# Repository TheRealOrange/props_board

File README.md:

# props_board
ESP32 based control board for costumes and props featuring USB PD enabled charging

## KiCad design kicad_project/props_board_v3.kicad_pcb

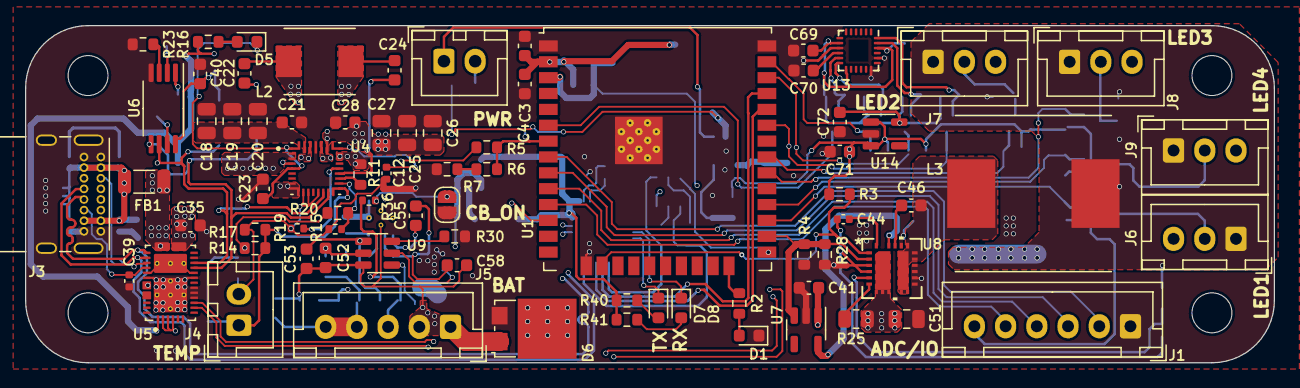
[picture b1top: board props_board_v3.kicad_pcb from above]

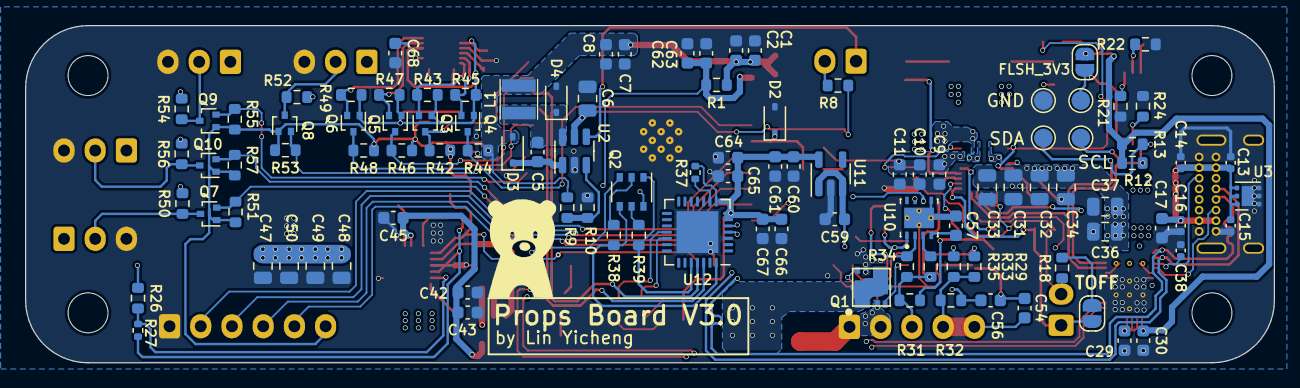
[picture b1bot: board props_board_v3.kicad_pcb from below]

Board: 4 copper layers, 100.0 x 27.0 mm, 187 parts (105 on the bottom side), 104 nets.

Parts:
C1, C2, C7, C8, C9, C10, C29, C30, C43, C61: 10u; C_0603_1608Metric
C3, C4, C5, C11, C21, C28, C35, C40, C41, C42, C46, C52, C53, C54, C55, C56, C58, C59, C60, C62, C63, C65, C67, C68, C69, C70, C71: 100n; C_0603_1608Metric
C6, C18, C19, C20, C25, C26, C27, C31, C32, C33, C34: 10u; C_0805_2012Metric
C12: 1000p; C_0402_1005Metric
C13, C14, C15, C16, C44: 10n; C_0402_1005Metric
C17, C23, C45, C64, C66: 4.7u; C_0603_1608Metric
C22, C24: 47n; C_0603_1608Metric
C36, C37, C47, C48, C49, C50, C51: 22u; C_0805_2012Metric
C38, C39: 330p; C_0402_1005Metric
C57: 330n; C_0603_1608Metric
C72: 1u; C_0603_1608Metric
D1, D5, D7, D8: LED; LED_0603_1608Metric
D2: MM3Z3V0ST1G; D_SOD-323
D3: 1N4148; D_SOD-323
D4: B5819WS; D_SOD-323
D6: SS10P4C; TO-277A
FB1: BLM31SN500SH1L; L_1206_3216Metric
H1, H2, H3, H4: MountingHole; MountingHole_3.2mm_M3_DIN965
J1: Conn_01x06; JST_XH_B6B-XH-A_1x06_P2.50mm_Vertical
J2: PWR; JST_XH_B2B-XH-A_1x02_P2.50mm_Vertical
J3: USB_C_Receptacle_USB2.0; USB_C_Receptacle_GCT_USB4085
J4: Conn_01x02; JST_XH_B2B-XH-A_1x02_P2.50mm_Vertical
J5: Conn_01x05; JST_XH_B5B-XH-A_1x05_P2.50mm_Vertical
J6: LED1; JST_XH_B3B-XH-A_1x03_P2.50mm_Vertical
J7: LED2; JST_XH_B3B-XH-A_1x03_P2.50mm_Vertical
J8: LED3; JST_XH_B3B-XH-A_1x03_P2.50mm_Vertical
J9: LED4; JST_XH_B3B-XH-A_1x03_P2.50mm_Vertical
JP1, JP2, JP3: Jumper_2_Open; SolderJumper-2_P1.3mm_Open_RoundedPad1.0x1.5mm
L1: 15u; TYA3012
L2: 1u; IND_ASPI-0530HI-1R0M-T2
L3: 3.3u; INDM1250X1250X600
NT1, NT2: NetTie_2; NetTie-2_SMD_Pad0.5mm
Q1: AON7804; DFN3X3
Q2: BC817DS; TSOP-6_1.65x3.05mm_P0.95mm
Q3, Q4, Q5, Q6, Q7, Q8, Q9, Q10: RE1C002UNTCL; SOT-416
R1, R3, R4, R5, R6, R7, R8, R10, R18, R21, R22, R23, R24, R28, R38, R39: 10k; R_0603_1608Metric
R2, R12, R13, R16, R30, R40, R41, R42, R43, R44, R45, R46, R47, R48, R49, R50, R51, R52, R53, R54, R55, R56, R57: 2k2; R_0603_1608Metric
R9, R17, R20, R26: 31.6k; R_0603_1608Metric
R11, R32, R35: 100; R_0603_1608Metric
R14: 5.23k; R_0603_1608Metric
R15, R36: 100k; R_0402_1005Metric
R19, R27: 6.04k; R_0402_1005Metric
R25: 200k; R_0805_2012Metric
R29, R31, R34: 270; R_0603_1608Metric
R33: 160; R_0603_1608Metric
R37: 1k; R_0402_1005Metric
TP1: FLSH_3V3; TestPoint_Pad_D1.5mm
TP2: SDA; TestPoint_Pad_D1.5mm
TP3: SCL; TestPoint_Pad_D1.5mm
TP4: GND; TestPoint_Pad_D1.5mm
U1: ESP32-WROOM-32U
U2: MCP16301; SOT-23-6
U3: TVS2200DRV; WSON-6-1EP_2x2mm_P0.65mm_EP1x1.6mm
U4: BQ25798RQMR; IC_BQ25798RQMR
U5: TPS25750DRJKR; IC_TPS25750DRJKR
U6: CAT24C256; TSSOP-8_4.4x3mm_P0.65mm
U7, U11: AP7375; SOT-23-5
U8: AOZ2261AQI-15; QFN4X4-22L_EP2_S_AOS
U9: S-8252; SOT-23-6
U10: BQ29209DRBR; SON65P300X300X100-9N
U12: CP2102N-Axx-xQFN28; QFN-28-1EP_5x5mm_P0.5mm_EP3.35x3.35mm
U13: ICM-20948; InvenSense_QFN-24_3x3mm_P0.4mm
U14: TLV74118; SOT-23-5

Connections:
/3V3: C1.1, C2.1, C3.1, C4.1, C7.1, C8.1, C71.1, D3.2 (A), J1.6, L1.2, Q7.1 (G), Q8.1 (G), Q9.1 (G), Q10.1 (G), R1.1, R3.1, R9.1, R42.1, R44.1, R46.1, R48.1, R51.1, R53.1, R55.1, R57.1, U1.2 (VDD), U14.1 (VIN), U14.3 (EN)
/3V3_EN: J2.1, U2.4 (EN)
/3V3_SW: C5.1, D4.1 (K), L1.1, U2.6 (SW)
/5V_PWR: C47.1, C48.1, C49.1, C50.1, J6.1, J7.1, J8.1, J9.1, L3.2, R26.1, R50.1, R52.1, R54.1, R56.1
/ADC1_CH4_GPIO: J1.2, U1.8 (IO32)
/ADC1_CH5_GPIO: J1.3, U1.9 (IO33)
/ADC2_CH8_GPIO: J1.4, U1.10 (IO25)
/ADC2_CH9_GPIO: J1.5, U1.11 (IO26)
/BAT_MON: C9.1, C10.1, C11.1, C54.1, J5.4, J5.5, R5.1, R11.2, R29.2, R32.1, R33.2, U4.22 (BAT), U4.23 (BAT__1)
/CB_EN: JP1.2 (B), R36.2, U1.12 (IO27), U10.6 (~CB_EN)
/EN: C62.1, C63.1, Q2.6 (C1), R1.2, U1.3 (EN)
/EN_5V: R4.1, R28.1, U1.26 (IO4), U7.3 (EN), U8.2 (EN)
/ESP_RXD: U1.34 (RXD0/IO3), U12.26 (TXD)
/ESP_SCL: Q5.3 (D), R46.2, U1.36 (IO22), U5.9 (I2CS_SCL)
/ESP_SDA: Q6.3 (D), R48.2, U1.33 (IO21), U5.8 (I2CS_SDA)
/ESP_TXD: U1.35 (TXD0/IO1), U12.25 (RXD)
/FSYNC: Q4.3 (D), R44.2, U1.6 (IO34)
/IND_LED: R2.1, U1.24 (IO2)
/INT: Q3.3 (D), R42.2, U1.37 (IO23)
/IO0: Q2.3 (C2), U1.25 (IO0)
/LED1: Q7.2 (S), R51.2, U1.27 (IO16)
/LED2: Q8.2 (S), R53.2, U1.31 (IO19)
/LED3: Q9.2 (S), R55.2, U1.30 (IO18)
/LED4: Q10.2 (S), R57.2, U1.28 (IO17)
/PGOOD_5V: R3.2, U1.16 (IO13), U8.1 (PGOOD)
/VBAT_SENSE: D2.1 (K), R5.2, R6.1, U1.7 (IO35)
/battery_charging/CC1: C38.1, J3.A5 (CC1), U5.28 (CC1)
/battery_charging/CC2: C39.1, J3.B5 (CC2), U5.29 (CC2)
/battery_charging/C_USB_N: J3.A7 (D-), J3.B7 (D-), U5.27 (GPIO5(USB_N)), U12.5 (D-)
/battery_charging/C_USB_P: J3.A6 (D+), J3.B6 (D+), U5.26 (GPIO4(USB_P)), U12.4 (D+)
/battery_charging/FLASH_3V3: C40.1, JP3.1 (A), TP1.1, U6.8 (VCC)
/battery_charging/I2C_M_SCL: R12.2, TP3.1, U4.14 (SCL), U5.17 (I2CM_SCL), U6.6 (SCL)
/battery_charging/I2C_M_SDA: R13.2, TP2.1, U4.15 (SDA), U5.16 (I2CM_SDA), U6.5 (SDA)
/battery_charging/ILIM_HIZ: R15.1, R20.2, U4.17 (ILIM_HIZ)
/battery_charging/LDO_1V5: C29.1, U5.2 (ADCIN1), U5.3 (ADCIN2), U5.4 (LDO_1V5)
/battery_charging/LDO_3V3: C30.1, JP3.2 (B), R12.1, R13.1, R16.1, U5.1 (LDO_3V3)
/battery_charging/PMID: C18.1, C19.1, C20.1, C21.1, U4.29 (PMID)
/battery_charging/PPHV: C31.1, C32.1, C33.1, C34.1, C35.1, C36.1, C37.1, U4.2 (VBUS), U4.3 (VBUS__1), U4.8 (VAC2), U4.9 (VAC1), U5.20_22 (PPHV)
/battery_charging/PROG: R19.1, U4.20 (PROG)
/battery_charging/REGN: C23.1, D5.1 (K), R14.1, R20.1, U4.1 (STAT), U4.5 (REGN)
/battery_charging/SW1: C22.1, L2.2, U4.28 (SW1)
/battery_charging/SW2: C24.1, L2.1, U4.26 (SW2)
/battery_charging/TS: J4.1, JP2.2 (B), R14.2, R17.1, U4.16 (TS)
/battery_charging/VBUS: C59.1, FB1.2, U5.23_25 (VBUS_IN), U5.32_33 (VBUS), U11.1 (VIN), U11.3 (EN)
/battery_protection/BATOUT: C52.2, C53.2, C54.2, C56.2, C57.2, C58.2, D6.1 (A), J5.1, J5.2, Q1.S2 (S), U9.6 (VSS), U10.5 (GND), U10.9 (EXP)
/battery_protection/CMN_DRN: D6.3 (K), Q1.D1 (D), Q1.D2 (D)
/imu/FSYNC_1V8: Q4.2 (S), R45.2, U13.11 (FSYNC)
/imu/IMU_1V8: C68.1, C69.1, C72.1, Q3.1 (G), Q4.1 (G), Q5.1 (G), Q6.1 (G), R43.1, R45.1, R47.1, R49.1, U13.8 (VDDIO), U13.13 (VDD), U13.22 (~CS), U14.5 (VOUT)
/imu/INT_1V8: Q3.2 (S), R43.2, U13.12 (INT1)
/imu/SCL_1V8: Q5.2 (S), R47.2, U13.23 (SCL/SCLK)
/imu/SDA_1V8: Q6.2 (S), R49.2, U13.24 (SDA/SDI)
/power_reg/5V_LDO: C42.1, C43.1, C45.1, U7.5 (VOUT), U8.21 (VCC)
/usb_uart/5V_UART_LDO: C60.1, C61.1, C64.1, C65.1, C66.1, C67.1, R37.1, R40.1, R41.1, U11.5 (VOUT), U12.6 (VDD), U12.7 (VREGIN), U12.8 (VBUS)
/usb_uart/DTR: Q2.4 (E2), R38.1, U12.28 (~DTR)
/usb_uart/RTS: Q2.1 (E1), R39.1, U12.24 (~RTS)
GND: C1.2, C2.2, C3.2, C4.2, C6.2, C7.2, C8.2, C9.2, C10.2, C11.2, C13.2, C14.2, C15.2, C16.2, C17.2, C18.2, C19.2, C20.2, C21.2, C23.2, C25.2, C26.2, C27.2, C28.2, C29.2, C30.2, C31.2, C32.2, C33.2, C34.2, C35.2, C36.2, C37.2, C38.2, C39.2, C40.2, C41.2, C42.2, C43.2, C45.2, C47.2, C48.2, C49.2, C50.2, C51.2, C59.2, C60.2, C61.2, C62.2, C63.2, C64.2, C65.2, C66.2, C67.2, C68.2, C69.2, C70.2, C71.2, C72.2, D1.1 (K), D2.2 (A), D4.2 (A), D6.2 (A), J1.1, J3.A1 (GND), J3.A12 (GND), J3.B1 (GND), J3.B12 (GND), J3.S1 (SHIELD), J6.3, J7.3, J8.3, J9.3, JP1.1 (A), NT1.2, NT2.2, Q1.S1 (S), R4.2, R7.2, R10.2, R21.2, R22.2, R23.2, R24.2, R28.2, R30.2, TP4.1, U1.1 (GND), U1.15 (GND), U1.38 (GND), U1.39 (GND), U2.2 (GND), U3.1 (GND), U3.2 (GND), U3.3 (GND), U3.7 (GND), U4.27 (GND), U5.10 (~I2CS_IRQ), U5.11 (GND), U5.12 (GND__1), U5.14 (GND__2), U5.18 (~I2CM_IRQ), U5.31 (GND__3), U5.39 (EXP_GND), U6.4 (GND), U7.2 (GND), U8.12 (PGND), U8.13 (PGND), U8.14 (PGND), U8.15 (PGND), U8.19 (PGND), U11.2 (GND), U12.3 (GND), U12.29 (GND), U13.9 (SDO/AD0), U13.18 (GND), U13.20 (GND), U14.2 (GND)
GND1: C44.2, NT2.1, R27.2, U8.3 (*PFM), U8.4 (AGND)
GNDA: C12.2, J4.2, NT1.1, R15.2, R17.2, R18.2, R19.2, U4.10 (ACDRV2), U4.11 (ACDRV1), U4.13 (~CE)
IN: C6.1, C25.1, C26.1, C27.1, C28.1, C41.1, C51.1, R8.2, R25.1, U2.5 (Vin), U4.25 (SYS), U7.1 (VIN), U8.7 (IN), U8.8 (IN), U8.9 (IN), U8.24 (IN)
LX: C46.2, L3.1, U8.10 (LX), U8.11 (LX), U8.16 (LX), U8.17 (LX), U8.18 (LX), U8.23 (LX)
unnamed: C13.1, C14.1, C15.1, C16.1, C17.1, FB1.1, J3.A4 (VBUS), J3.A9 (VBUS), J3.B4 (VBUS), J3.B9 (VBUS), U3.4 (IN), U3.5 (IN), U3.6 (IN)
unnamed: D1.2 (A), R2.2
unnamed: C5.2, D3.1 (K), U2.1 (BOOST)
unnamed: D5.2 (A), R16.2
unnamed: D7.2 (A), R40.2
unnamed: D7.1 (K), U12.19 (~TXT/GPIO.0)
unnamed: D8.2 (A), R41.2
unnamed: D8.1 (K), U12.18 (~RXT/GPIO.1)
unnamed: J2.2, R8.1
unnamed: J5.3, R31.2, R34.2, R35.2, R36.1
unnamed: J6.2, Q7.3 (D), R50.2
unnamed: J7.2, Q8.3 (D), R52.2
unnamed: J8.2, Q9.3 (D), R54.2
unnamed: J9.2, Q10.3 (D), R56.2
unnamed: JP2.1 (A), R18.1
unnamed: Q1.G1 (G), U9.2 (CO)
unnamed: Q1.G2 (G), U9.1 (DO)
unnamed: Q2.2 (B1), R38.2
unnamed: Q2.5 (B2), R39.2
unnamed: R6.2, R7.1
unnamed: R9.2, R10.1, U2.3 (Vfb)
unnamed: R11.1, U4.18 (BATP)
unnamed: C22.2, U4.4 (BTST1)
unnamed: C24.2, U4.19 (BTST2)
unnamed: C12.1, U4.24 (SDRV)
unnamed: U5.15 (DRAIN), U5.30 (DRAIN__1), U5.40 (EXP_DRAIN)
unnamed: R21.1, U6.1 (A0)
unnamed: R22.1, U6.2 (A1)
unnamed: R23.1, U6.3 (A2)
unnamed: R24.1, U6.7 (WP)
unnamed: C46.1, U8.20 (BST)
unnamed: R26.2, R27.1, U8.5 (FB)
unnamed: C44.1, U8.22 (SS)
unnamed: R25.2, U8.6 (TON)
unnamed: C53.1, R31.1, U9.4 (VC)
unnamed: C52.1, R29.1, U9.5 (VDD)
unnamed: R30.1, U9.3 (VM)
unnamed: C57.1, U10.4 (CD)
unnamed: C55.2, C58.1, R34.1, U10.2 (VC1)
unnamed: R35.1, U10.3 (VC1_CB)
unnamed: C55.1, R33.1, U10.1 (VC2)
unnamed: C56.1, R32.2, U10.7 (VDD)
unnamed: R37.2, U12.9 (~RST)
unnamed: C70.1, U13.10 (REGOUT)

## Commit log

2023-11-19 props board v3
2023-11-20 updated gitignore
